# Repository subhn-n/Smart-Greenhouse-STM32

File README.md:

# 🌱 Smart Greenhouse Controller

<p align="center">

</p>

---

## 📖 Overview

This project is a **smart greenhouse controller** designed around an **STM32L476RG** microcontroller.  
The goal was to create an embedded system capable of:

- 🌡 Monitoring temperature
- 💧 Monitoring soil humidity
- ☀️ Measuring ambient light
- 🚿 Controlling a water pump
- 🌬 Controlling a cooling fan
- 💡 Controlling LED lighting using PWM
- 📱 Communicating wirelessly through Bluetooth

The project combines:

- Embedded programming
- Power electronics
- PCB design
- Sensor acquisition
- Bluetooth communication
- PWM control
- Rapid prototyping

---

# 🧠 System Architecture

The system is divided into several functional blocks:

- 🔋 Power PCB
- ⚡ Actuator PCB
- 🌱 Sensor PCB
- 💡 LED Control PCB
- 🧠 STM32 Main Controller

---

# 🔌 Hardware Used

## 🧠 Microcontroller

| Component | Description |
|---|---|
| STM32L476RG | Main embedded controller |

---

## 🌱 Sensors

| Sensor | Purpose |
|---|---|
| DS18B20 | Temperature measurement |
| Capacitive Soil Sensor V2.0 | Soil humidity measurement |
| LDR | Ambient light measurement |

---

## ⚡ Actuators

| Component | Purpose |
|---|---|
| 5V Water Pump | Irrigation |
| 12V Fan | Cooling |
| 12V LED Modules | Artificial lighting |

---

# 📡 Bluetooth Communication

The system communicates with a smartphone using a **HM10 BLE module**.

Commands can be sent directly from a mobile device:

```txt
PUMP_ON
PUMP_OFF
FAN_ON
FAN_OFF
TEMP?
HUM?
LIGHT?
LED:500
```

The STM32 then responds with sensor values or activates the requested actuator.

---

# 💡 PWM LED Control

LED brightness is controlled using PWM generated by **TIM3**.

```txt
LED:0      -> OFF
LED:250    -> 25%
LED:500    -> 50%
LED:999    -> 100%
```

---

# 🛠 PCB Design

The project originally started as a single large shield PCB.

To improve modularity and debugging, the system was redesigned into multiple smaller PCBs:

- Power PCB
- Sensor PCB
- Actuator PCB
- LED PCB

This modular architecture made:
- testing easier,
- debugging faster,
- integration cleaner.

---

# 💻 Software

The firmware was developed using:

Main software features:

- UART communication
- ADC acquisition
- PWM generation
- Threshold-based alerts
- Sensor data processing
- Bluetooth command parsing

---

# 📱 Android Application

An Android application was also started using:

The goal was to create a dedicated greenhouse monitoring interface.

---

# 🧪 Testing

Each subsystem was validated independently:

- ✅ Pump control
- ✅ Fan control
- ✅ Bluetooth communication
- ✅ PWM LED control
- ✅ Temperature acquisition
- ✅ ADC acquisition
- ✅ Sensor threshold detection

The project was progressively integrated block-by-block during development.

---

# 🏗 Greenhouse Prototype

A physical greenhouse mockup was built to integrate the electronics into a realistic environment.

Materials used:

- Plexiglass
- Wood
- PVC bars
- Aluminum bars

---

# 🚀 Future Improvements

- 📲 Complete Android app
- 🤖 Automatic greenhouse regulation
- 📈 Data logging

---

# 👨‍💻 Authors

- subhn-n
- Trifano

ENSEA - Embedded Systems Project 🌱

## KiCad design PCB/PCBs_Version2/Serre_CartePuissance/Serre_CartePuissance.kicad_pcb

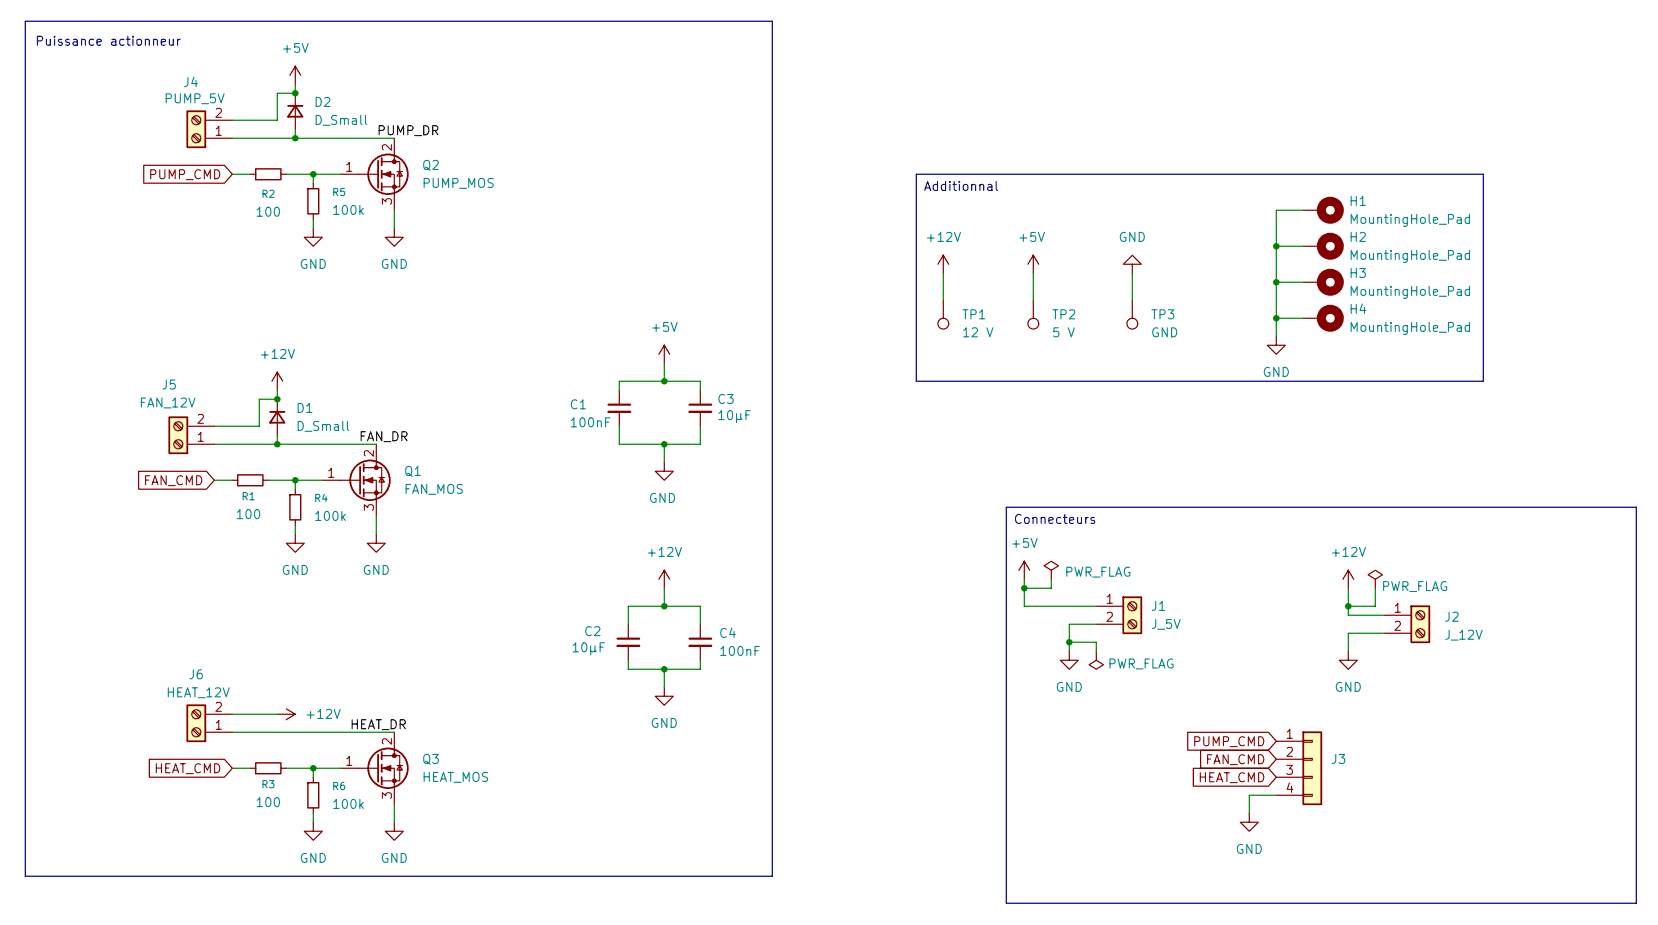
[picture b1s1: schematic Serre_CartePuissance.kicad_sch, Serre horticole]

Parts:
C1, C4: 100nF; C_0603_1608Metric_Pad1.08x0.95mm_HandSolder
C2, C3: 10µF; C_0805_2012Metric_Pad1.18x1.45mm_HandSolder
D1, D2: D_Small; D_SMB_Handsoldering
H1, H2, H3, H4: MountingHole_Pad; MountingHole_3.2mm_M3_DIN965_Pad
J1: J_5V; TerminalBlock_CUI_TB007-508-02_1x02_P5.08mm_Horizontal
J2: J_12V; TerminalBlock_CUI_TB007-508-02_1x02_P5.08mm_Horizontal
J3: Conn_01x04; PinSocket_1x04_P2.54mm_Vertical
J4: PUMP_5V; TerminalBlock_CUI_TB007-508-02_1x02_P5.08mm_Horizontal
J5: FAN_12V; TerminalBlock_CUI_TB007-508-02_1x02_P5.08mm_Horizontal
J6: HEAT_12V; TerminalBlock_CUI_TB007-508-02_1x02_P5.08mm_Horizontal
Q1: FAN_MOS; TO-252-2
Q2: PUMP_MOS; TO-252-2
Q3: HEAT_MOS; TO-252-2
R1, R2, R3: 100; R_0603_1608Metric_Pad0.98x0.95mm_HandSolder
R4, R5, R6: 100k; R_0603_1608Metric_Pad0.98x0.95mm_HandSolder
TP1: 12 V; TestPoint_Pad_D1.5mm
TP2: 5 V; TestPoint_Pad_D1.5mm
TP3: GND; TestPoint_Pad_D1.5mm

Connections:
+5V: C1.1, C3.1, D2.1 (K), J1.1, J4.2, TP2.1
+12V: C2.1, C4.1, D1.1 (K), J2.1, J5.2, J6.2, TP1.1
/FAN_DR: D1.2 (A), J5.1, Q1.2 (D)
/HEAT_DR: J6.1, Q3.2 (D)
/PUMP_DR: D2.2 (A), J4.1, Q2.2 (D)
FAN_CMD: J3.2, R1.1
GND: C1.2, C2.2, C3.2, C4.2, H1.1, H2.1, H3.1, H4.1, J1.2, J2.2, J3.4, Q1.3 (S), Q2.3 (S), Q3.3 (S), R4.2, R5.2, R6.2, TP3.1
HEAT_CMD: J3.3, R3.1
unnamed: Q1.1 (G), R1.2, R4.1
unnamed: Q2.1 (G), R2.2, R5.1
unnamed: Q3.1 (G), R3.2, R6.1
PUMP_CMD: J3.1, R2.1

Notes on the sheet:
Puissance actionneur
Connecteurs
Additionnal

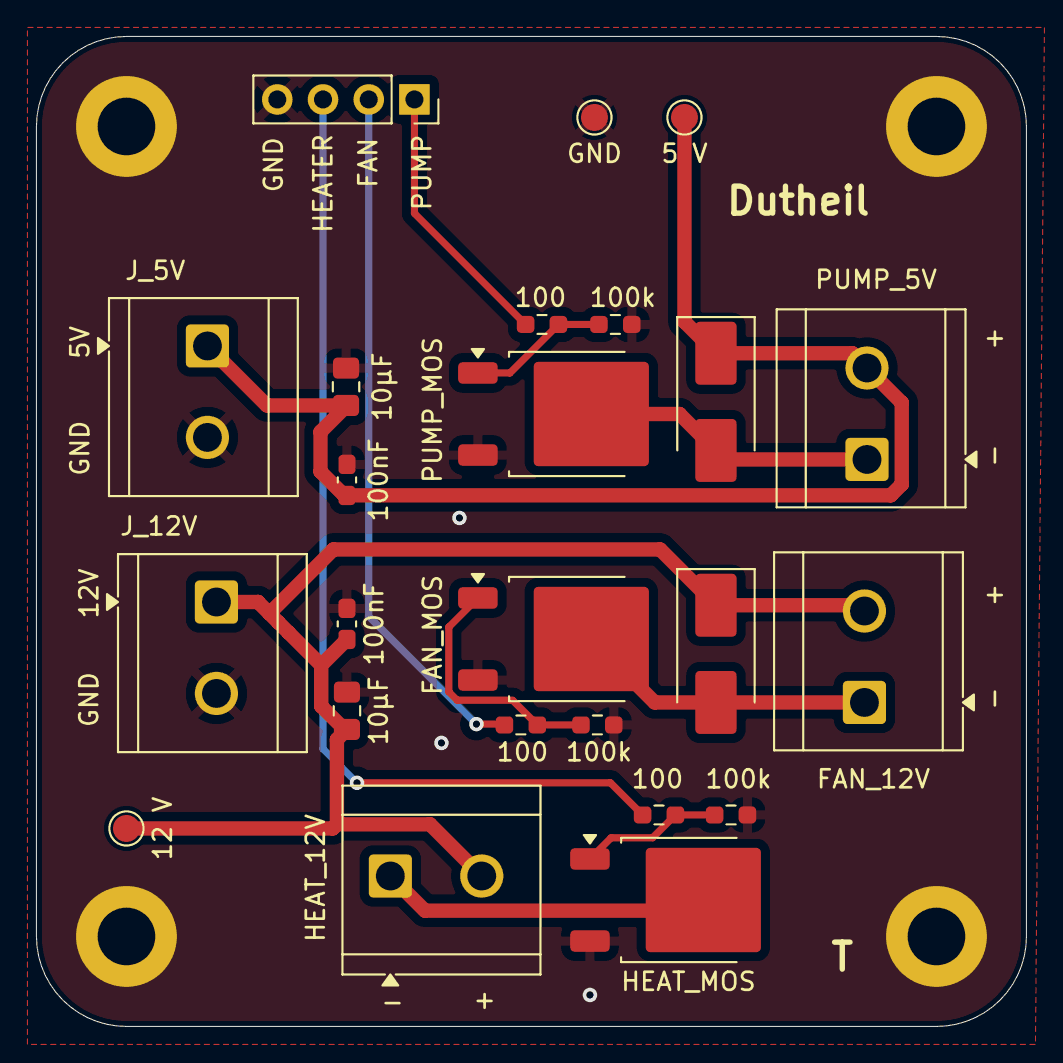
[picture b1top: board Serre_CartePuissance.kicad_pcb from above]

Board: 2 copper layers, 55.0 x 55.0 mm, 28 parts (0 on the bottom side), 12 nets.

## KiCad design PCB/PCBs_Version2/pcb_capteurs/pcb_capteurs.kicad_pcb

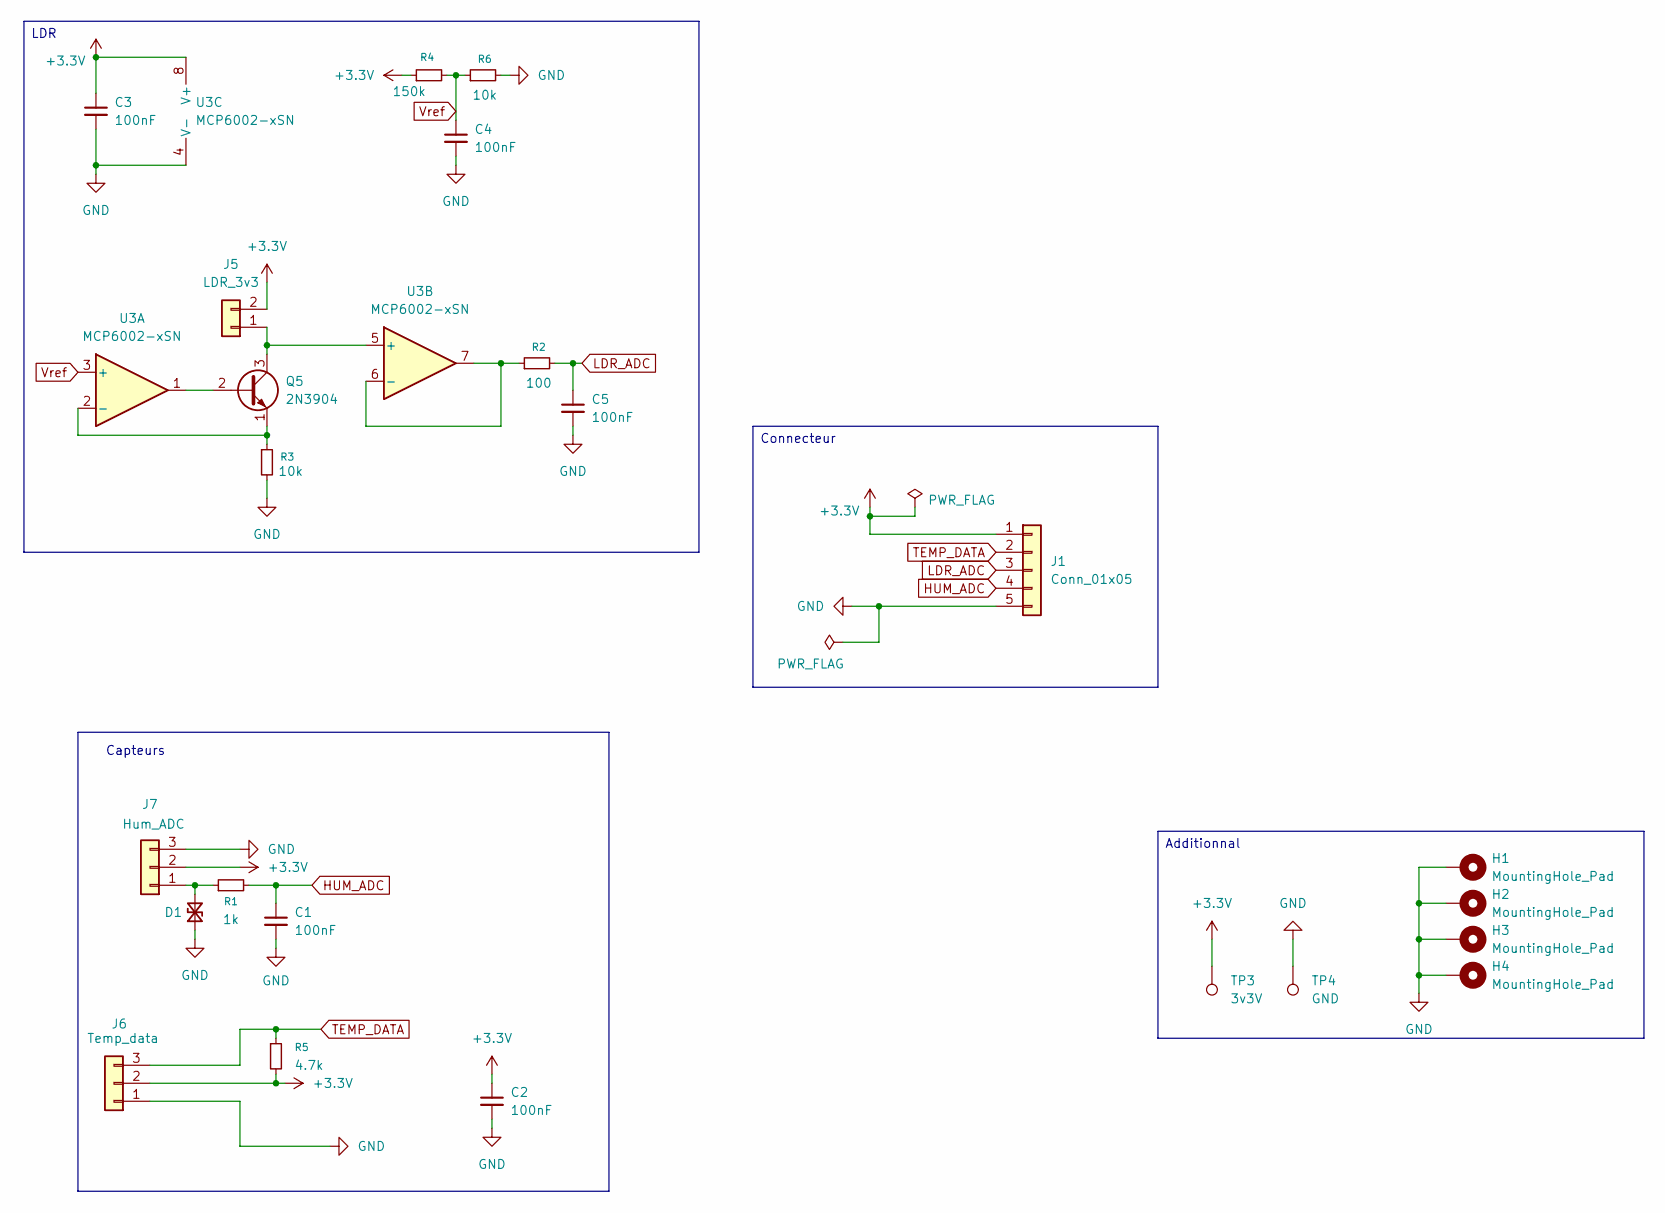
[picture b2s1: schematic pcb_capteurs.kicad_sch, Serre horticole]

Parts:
C1, C2, C3, C4, C5: 100nF; C_0603_1608Metric_Pad1.08x0.95mm_HandSolder
D1: D_TVS_Small; D_SMB_Handsoldering
H1, H2, H3, H4: MountingHole_Pad; MountingHole_3.2mm_M3_DIN965_Pad
J1: Conn_01x05; PinSocket_1x05_P2.54mm_Vertical
J5: LDR_3v3; PinSocket_1x02_P2.54mm_Vertical
J6: Temp_data; PinSocket_1x03_P2.54mm_Vertical
J7: Hum_ADC; PinSocket_1x03_P2.54mm_Vertical
Q5: 2N3904; TO-92_Inline_Wide
R1: 1k; R_0603_1608Metric_Pad0.98x0.95mm_HandSolder
R2: 100; R_0603_1608Metric_Pad0.98x0.95mm_HandSolder
R3, R6: 10k; R_0603_1608Metric_Pad0.98x0.95mm_HandSolder
R4: 150k; R_0603_1608Metric_Pad0.98x0.95mm_HandSolder
R5: 4.7k; R_0603_1608Metric_Pad0.98x0.95mm_HandSolder
TP3: 3v3V; TestPoint_Pad_D1.5mm
TP4: GND; TestPoint_Pad_D1.5mm
U3: MCP6002-xSN; SOIC-8_3.9x4.9mm_P1.27mm

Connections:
+3.3V: C2.1, C3.1, J1.1, J5.2, J6.2, J7.2, R4.1, R5.2, TP3.1, U3.8 (V+)
GND: C1.2, C2.2, C3.2, C4.2, C5.2, D1.1 (A1), H1.1, H2.1, H3.1, H4.1, J1.5, J6.1, J7.3, R3.2, R6.2, TP4.1, U3.4 (V-)
HUM_ADC: C1.1, J1.4, R1.2
LDR_ADC: C5.1, J1.3, R2.2
unnamed: D1.2 (A2), J7.1, R1.1
unnamed: J5.1, Q5.3 (C), U3.5 (+)
unnamed: Q5.2 (B), U3.1
unnamed: Q5.1 (E), R3.1, U3.2 (-)
unnamed: R2.1, U3.6 (-), U3.7
TEMP_DATA: J1.2, J6.3, R5.1
Vref: C4.1, R4.2, R6.1, U3.3 (+)

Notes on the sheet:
Capteurs
Additionnal
Connecteur
LDR

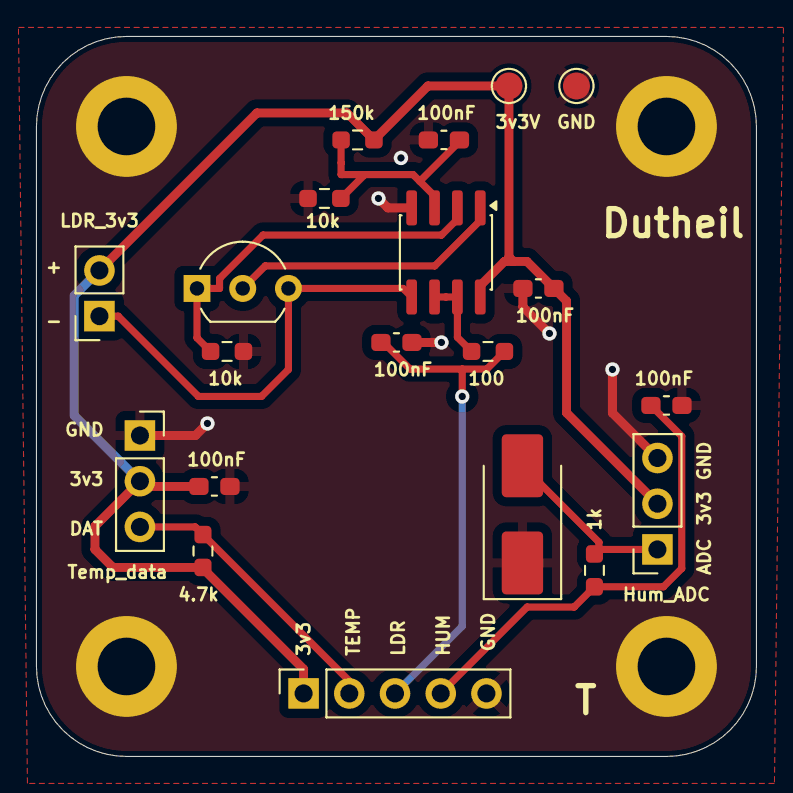
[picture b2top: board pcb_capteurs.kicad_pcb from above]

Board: 2 copper layers, 40.0 x 40.0 mm, 24 parts (0 on the bottom side), 11 nets.

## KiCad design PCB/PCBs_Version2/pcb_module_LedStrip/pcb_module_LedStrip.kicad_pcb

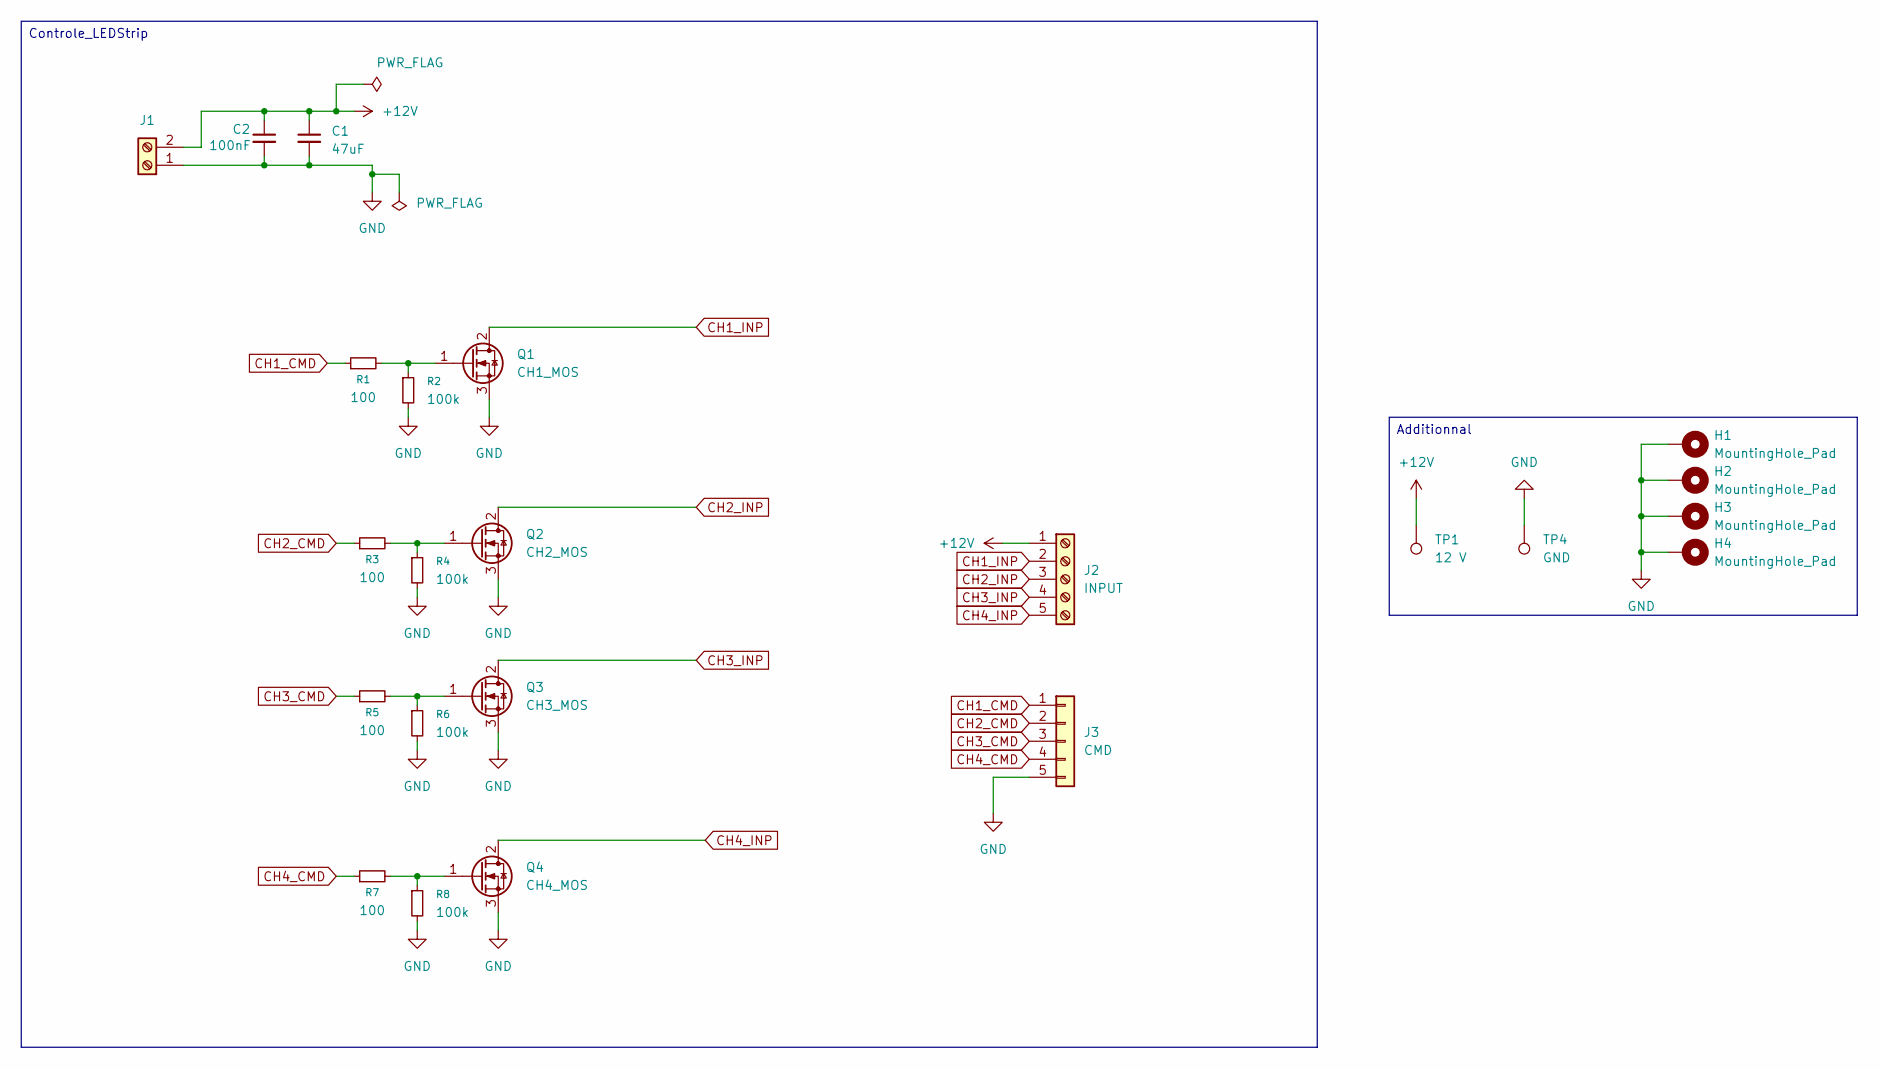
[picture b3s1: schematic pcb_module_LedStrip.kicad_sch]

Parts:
C1: 47uF; CP_Radial_D5.0mm_P2.00mm
C2: 100nF; C_0603_1608Metric_Pad1.08x0.95mm_HandSolder
H1, H2, H3, H4: MountingHole_Pad; MountingHole_3.2mm_M3_DIN965_Pad
J1: Screw_Terminal_01x02; TerminalBlock_CUI_TB007-508-02_1x02_P5.08mm_Horizontal
J2: INPUT; TerminalBlock_CUI_TB007-508-05_1x05_P5.08mm_Horizontal
J3: CMD; PinSocket_1x05_P2.54mm_Vertical
Q1: CH1_MOS; TO-252-2
Q2: CH2_MOS; TO-252-2
Q3: CH3_MOS; TO-252-2
Q4: CH4_MOS; TO-252-2
R1, R3, R5, R7: 100; R_0603_1608Metric_Pad0.98x0.95mm_HandSolder
R2, R4, R6, R8: 100k; R_0603_1608Metric_Pad0.98x0.95mm_HandSolder
TP1: 12 V; TestPoint_Pad_D1.5mm
TP4: GND; TestPoint_Pad_D1.5mm

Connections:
+12V: C1.1, C2.1, J1.2, J2.1, TP1.1
CH1_CMD: J3.1, R1.1
CH1_INP: J2.2, Q1.2 (D)
CH2_CMD: J3.2, R3.1
CH2_INP: J2.3, Q2.2 (D)
CH3_CMD: J3.3, R5.1
CH3_INP: J2.4, Q3.2 (D)
CH4_CMD: J3.4, R7.1
CH4_INP: J2.5, Q4.2 (D)
GND: C1.2, C2.2, H1.1, H2.1, H3.1, H4.1, J1.1, J3.5, Q1.3 (S), Q2.3 (S), Q3.3 (S), Q4.3 (S), R2.2, R4.2, R6.2, R8.2, TP4.1
unnamed: Q1.1 (G), R1.2, R2.1
unnamed: Q2.1 (G), R3.2, R4.1
unnamed: Q3.1 (G), R5.2, R6.1
unnamed: Q4.1 (G), R7.2, R8.1

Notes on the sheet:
Additionnal
Controle_LEDStrip

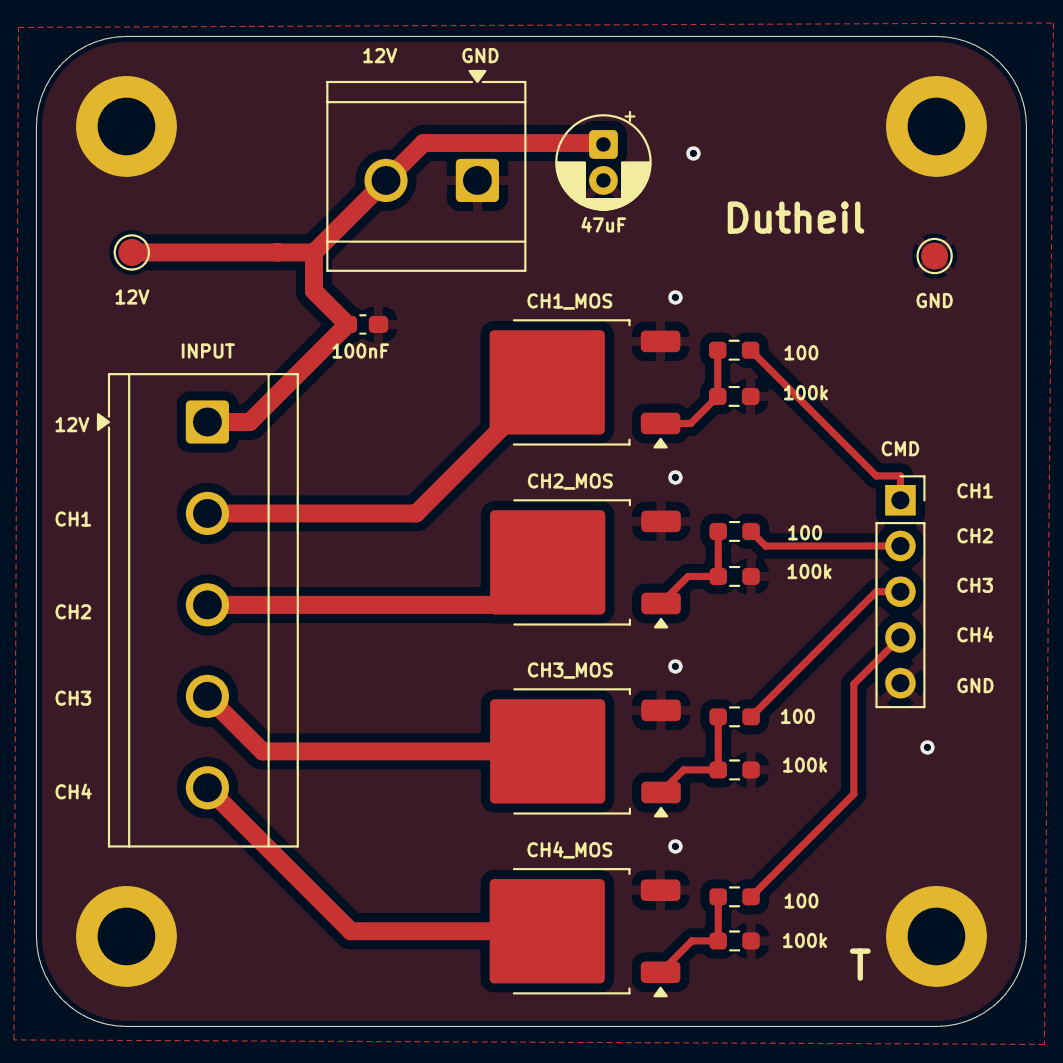
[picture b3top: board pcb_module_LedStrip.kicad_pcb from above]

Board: 2 copper layers, 55.0 x 55.0 mm, 23 parts (0 on the bottom side), 14 nets.

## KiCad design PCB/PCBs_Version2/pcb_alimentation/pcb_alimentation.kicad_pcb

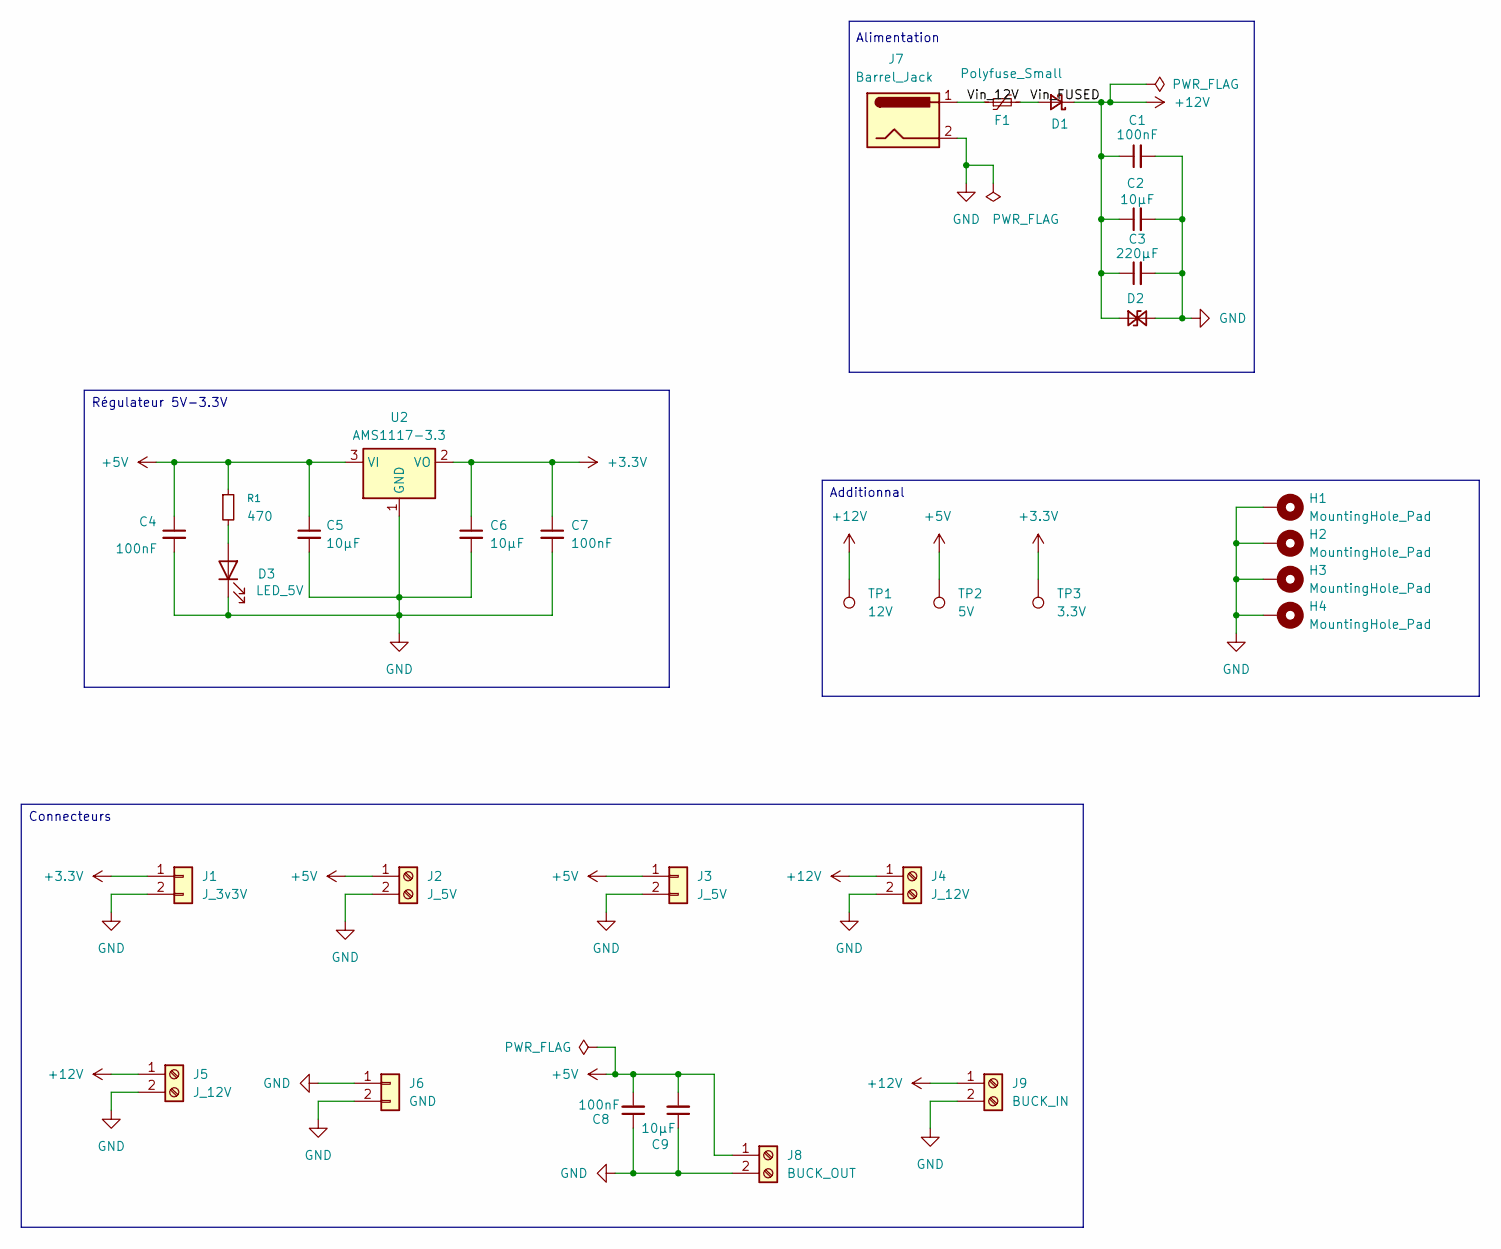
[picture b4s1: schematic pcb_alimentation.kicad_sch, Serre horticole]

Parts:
C1, C4, C7, C8: 100nF; C_0603_1608Metric_Pad1.08x0.95mm_HandSolder
C2, C5, C6, C9: 10µF; C_0805_2012Metric_Pad1.18x1.45mm_HandSolder
C3: 220µF; CP_Radial_D8.0mm_P3.50mm
D1: D_Schottky_Small; D_SMB_Handsoldering
D2: D_TVS_Small; D_SMB_Handsoldering
D3: LED_5V; LED_0805_2012Metric_Pad1.15x1.40mm_HandSolder
F1: Polyfuse_Small; Fuse_2920_7451Metric_Pad2.10x5.45mm_HandSolder
H1, H2, H3, H4: MountingHole_Pad; MountingHole_3.2mm_M3_DIN965_Pad
J1: J_3v3V; PinHeader_1x02_P2.54mm_Vertical
J2: J_5V; TerminalBlock_CUI_TB007-508-02_1x02_P5.08mm_Horizontal
J3: J_5V; PinHeader_1x02_P2.54mm_Vertical
J4, J5: J_12V; TerminalBlock_CUI_TB007-508-02_1x02_P5.08mm_Horizontal
J6: GND; PinHeader_1x02_P2.54mm_Vertical
J7: Barrel_Jack; BarrelJack_Horizontal
J8: BUCK_OUT; TerminalBlock_CUI_TB007-508-02_1x02_P5.08mm_Horizontal
J9: BUCK_IN; TerminalBlock_CUI_TB007-508-02_1x02_P5.08mm_Horizontal
R1: 470; R_0603_1608Metric_Pad0.98x0.95mm_HandSolder
TP1: 12V; TestPoint_Pad_D1.5mm
TP2: 5V; TestPoint_Pad_D1.5mm
TP3: 3.3V; TestPoint_Pad_D1.5mm
U2: AMS1117-3.3; SOT-223-3_TabPin2

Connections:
+3.3V: C6.1, C7.1, J1.1, TP3.1, U2.2 (VO)
+5V: C4.1, C5.1, C8.2, C9.2, J2.1, J3.1, J8.1, R1.1, TP2.1, U2.3 (VI)
+12V: C1.1, C2.1, C3.1, D1.1 (K), D2.1 (A1), J4.1, J5.1, J9.1, TP1.1
/Vin_12V: F1.1, J7.1
/Vin_FUSED: D1.2 (A), F1.2
GND: C1.2, C2.2, C3.2, C4.2, C5.2, C6.2, C7.2, C8.1, C9.1, D2.2 (A2), D3.1 (K), H1.1, H2.1, H3.1, H4.1, J1.2, J2.2, J3.2, J4.2, J5.2, J6.1, J6.2, J7.2, J8.2, J9.2, U2.1 (GND)
unnamed: D3.2 (A), R1.2

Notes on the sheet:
Alimentation
Régulateur 5V-3.3V
Additionnal
Connecteurs

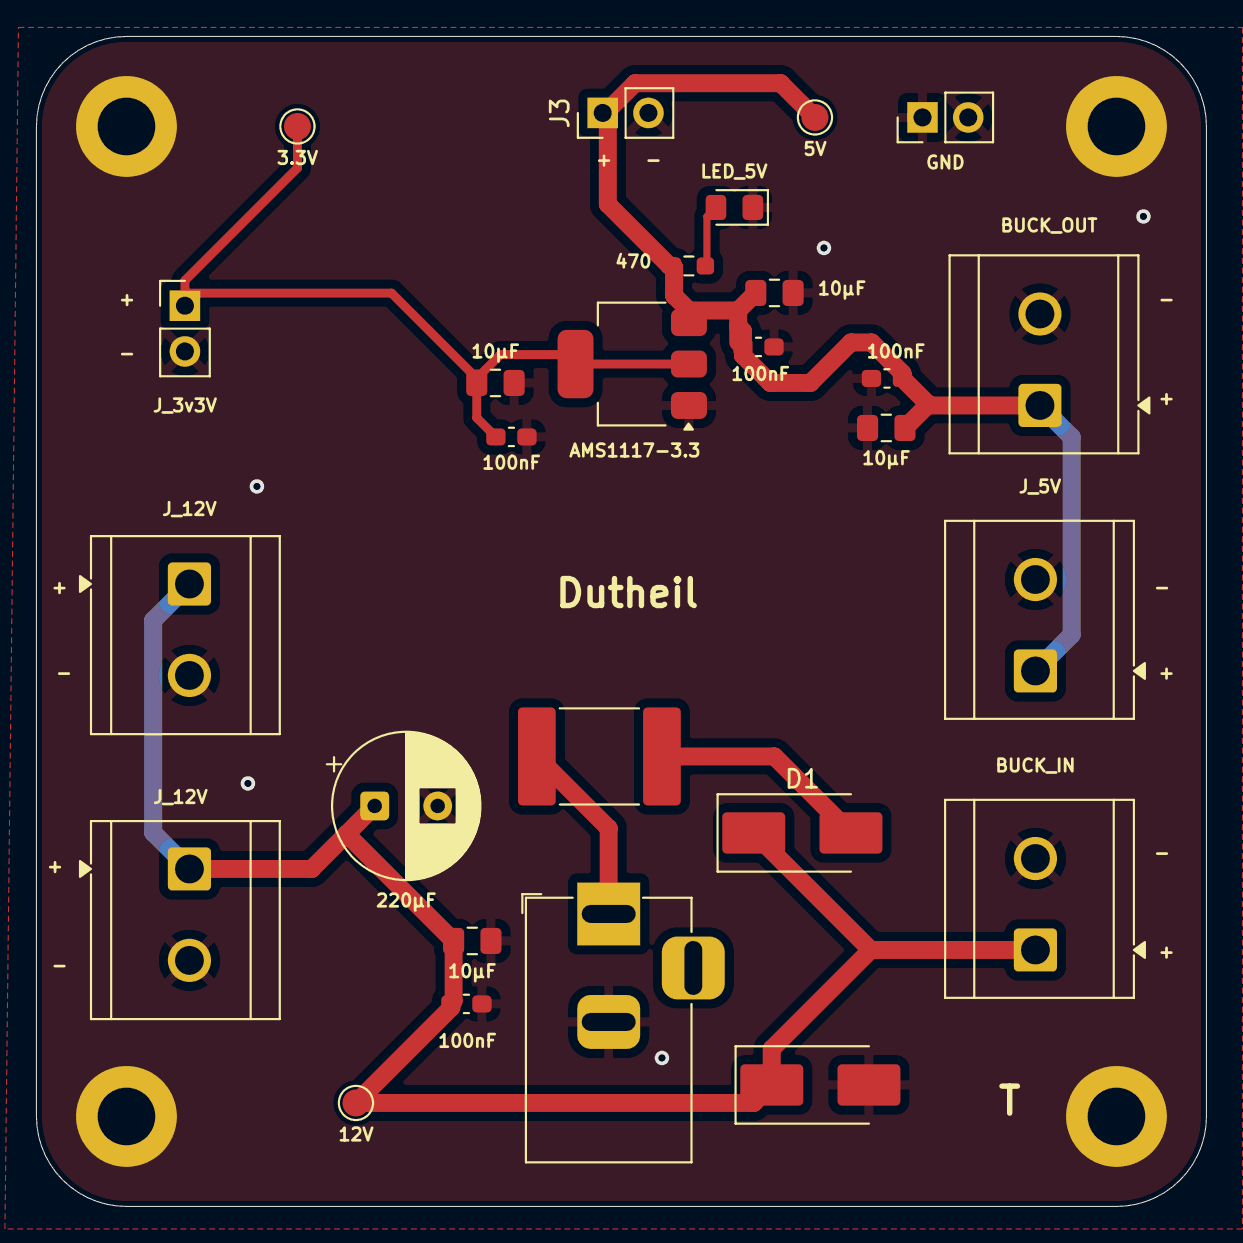
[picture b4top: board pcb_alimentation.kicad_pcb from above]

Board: 2 copper layers, 65.0 x 65.0 mm, 31 parts (0 on the bottom side), 7 nets.

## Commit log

2026-05-16 ajout des fichiers PCB
2026-05-20 Ajout des test des composants version 1
2026-05-21 Create Maquette
2026-05-22 Petits changements de maquette PCB
2026-05-23 refactoring, ajout du code et du rapport
2026-05-24 modif du readme
2026-05-24 ajout de la diapo
